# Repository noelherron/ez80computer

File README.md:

# eZ80Computer

This is a single board computer based on the Zilog eZ80 microcontroller.

The eZ80 was chosen because it is an interesting microcontroller with a deep history.

It's CPU is based on the Z80, which was very popular in the 1980s, and is still manufactured today.

The eZ80 is distinct from many other microcontrollers because it has an exposed address and data bus.

Most microcontrollers have built in memory and omit these pins.

This means we can design our own memory scheme, and learn about things like bus mastering.

Like a traditional microcontroller, it still has many built in periferals, which keeps things small and simple.

This is a learning project for me to better understand electronics, PCB design, and computer system design.

I have already spent many hours in KiCad and had a batch of prototypes made.

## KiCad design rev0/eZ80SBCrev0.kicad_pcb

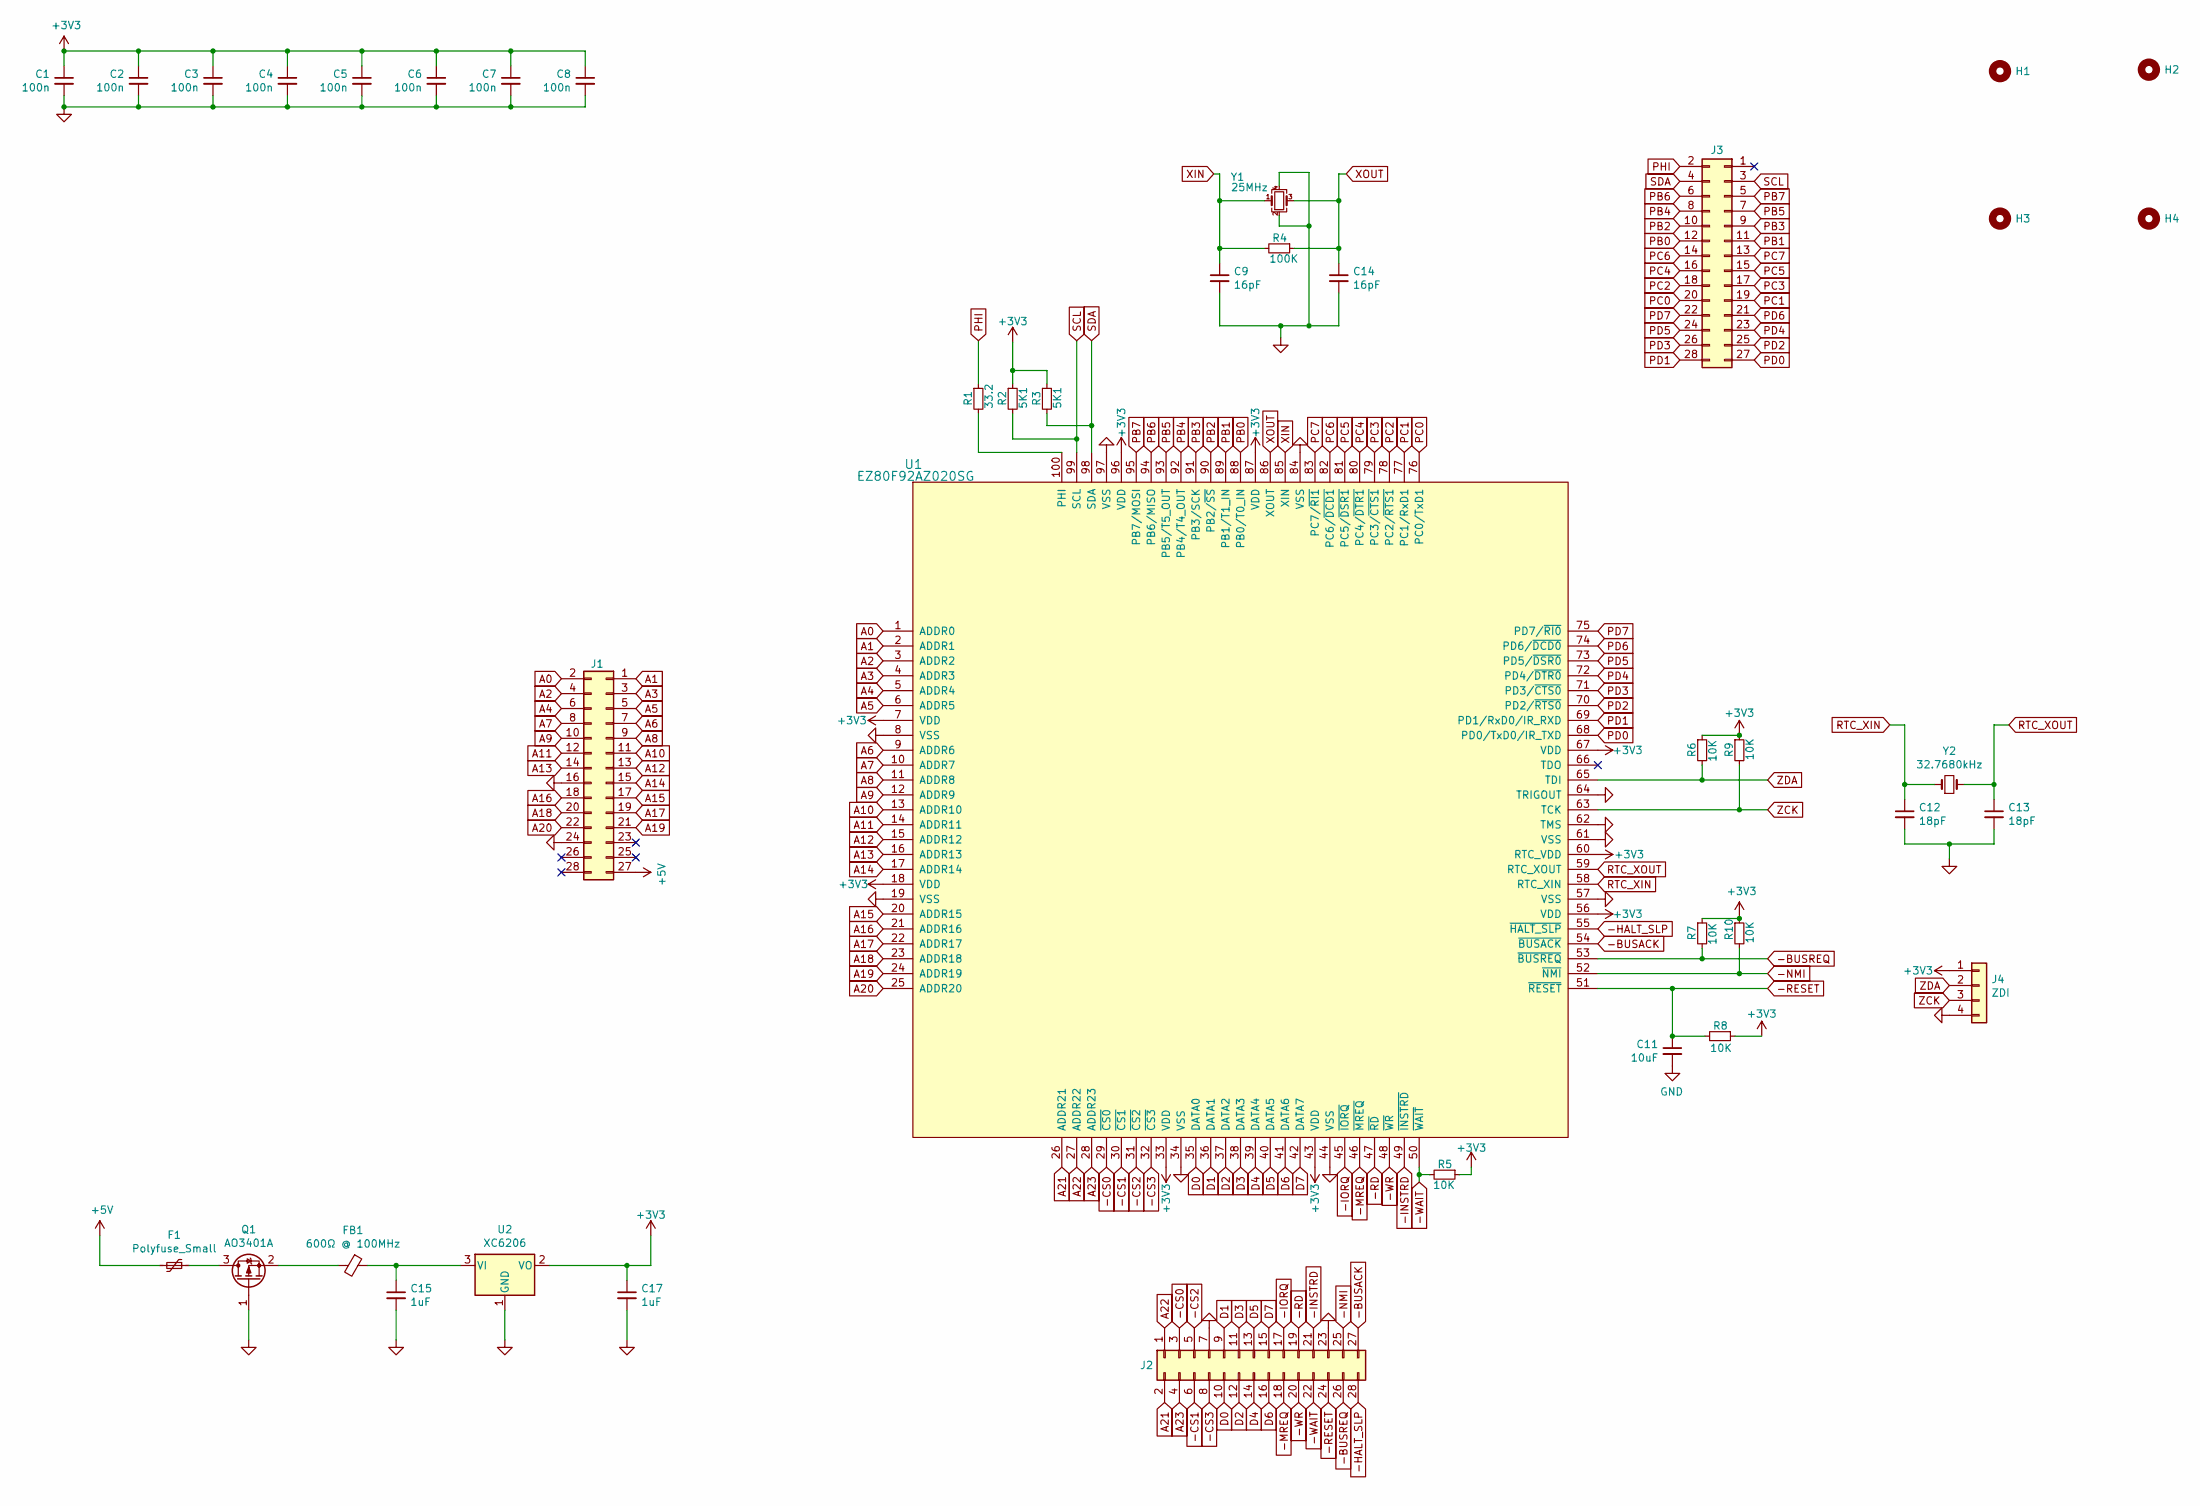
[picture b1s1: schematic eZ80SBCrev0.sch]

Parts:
C1, C2, C3, C4, C5, C6, C7, C8: 100n; C_0402_1005Metric; MFR. PART# CL05B104KO5NNNC; LCSC C1525
C9, C14: 16pF; C_0805_2012Metric; LCSC C1794
C11: 10uF; C_0402_1005Metric; MFR. PART# CL05A106MQ5NUNC; LCSC C15525
C12, C13: 18pF; C_0402_1005Metric; LCSC C1549
C15, C17: 1uF; C_0805_2012Metric; LCSC C28323
F1: Polyfuse_Small; Fuse_0805_2012Metric
FB1: 600Ω @ 100MHz; L_0805_2012Metric; LCSC C1017
H1, H2, H3, H4: MountingHole; MountingHole_2.1mm
J1, J2, J3: Conn_02x14_Top_Bottom; PinSocket_2x14_P2.54mm_Vertical
J4: ZDI; PinHeader_1x04_P2.54mm_Vertical
Q1: AO3401A; SOT-23; LCSC C15127
R1: 33.2; R_0402_1005Metric; MFR. PART# 0402WGF5101TCE; LCSC C25905
R2, R3: 5K1; R_0402_1005Metric; MFR. PART# 0402WGF5101TCE; LCSC C25905
R4: 100K; R_0805_2012Metric; LCSC C17407
R5, R6, R7, R8, R9, R10: 10K; R_0402_1005Metric; MFR. PART# 0402WGF1002TCE; LCSC C25744
U1: EZ80F92AZ020SG; LQFP-100_14x14mm_P0.5mm
U2: XC6206; SOT-23; LCSC C5446
Y1: 25MHz; SMD-5032-4P; LCSC C9006
Y2: 32.7680kHz; Crystal_SMD_3215-2Pin_3.2x1.5mm; LCSC C32346

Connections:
+3V3: C1.1, C2.1, C3.1, C4.1, C5.1, C6.1, C7.1, C8.1, C17.1, J4.1, R2.1, R3.1, R5.1, R6.1, R7.1, R8.1, R9.1, R10.1, U1.7 (VDD), U1.18 (VDD), U1.33 (VDD), U1.43 (VDD), U1.56 (VDD), U1.60 (RTC_VDD), U1.67 (VDD), U1.87 (VDD), U1.96 (VDD), U2.2 (VO)
+5V: F1.2, J1.27
-BUSACK: J2.27, U1.54 (~BUSACK)
-BUSREQ: J2.26, R7.2, U1.53 (~BUSREQ)
-CS0: J2.3, U1.29 (~CS0)
-CS1: J2.6, U1.30 (~CS1)
-CS2: J2.5, U1.31 (~CS2)
-CS3: J2.8, U1.32 (~CS3)
-HALT_SLP: J2.28, U1.55 (~HALT_SLP)
-INSTRD: J2.21, U1.49 (~INSTRD)
-IORQ: J2.17, U1.45 (~IORQ)
-MREQ: J2.18, U1.46 (~MREQ)
-NMI: J2.25, R10.2, U1.52 (~NMI)
-RD: J2.19, U1.47 (~RD)
-RESET: C11.1, J2.24, R8.2, U1.51 (~RESET)
-WAIT: J2.22, R5.2, U1.50 (~WAIT)
-WR: J2.20, U1.48 (~WR)
A0: J1.2, U1.1 (ADDR0)
A1: J1.1, U1.2 (ADDR1)
A2: J1.4, U1.3 (ADDR2)
A3: J1.3, U1.4 (ADDR3)
A4: J1.6, U1.5 (ADDR4)
A5: J1.5, U1.6 (ADDR5)
A6: J1.7, U1.9 (ADDR6)
A7: J1.8, U1.10 (ADDR7)
A8: J1.9, U1.11 (ADDR8)
A9: J1.10, U1.12 (ADDR9)
A10: J1.11, U1.13 (ADDR10)
A11: J1.12, U1.14 (ADDR11)
A12: J1.13, U1.15 (ADDR12)
A13: J1.14, U1.16 (ADDR13)
A14: J1.15, U1.17 (ADDR14)
A15: J1.17, U1.20 (ADDR15)
A16: J1.18, U1.21 (ADDR16)
A17: J1.19, U1.22 (ADDR17)
A18: J1.20, U1.23 (ADDR18)
A19: J1.21, U1.24 (ADDR19)
A20: J1.22, U1.25 (ADDR20)
A21: J2.2, U1.26 (ADDR21)
A22: J2.1, U1.27 (ADDR22)
A23: J2.4, U1.28 (ADDR23)
D0: J2.10, U1.35 (DATA0)
D1: J2.9, U1.36 (DATA1)
D2: J2.12, U1.37 (DATA2)
D3: J2.11, U1.38 (DATA3)
D4: J2.14, U1.39 (DATA4)
D5: J2.13, U1.40 (DATA5)
D6: J2.16, U1.41 (DATA6)
D7: J2.15, U1.42 (DATA7)
GND: C1.2, C2.2, C3.2, C4.2, C5.2, C6.2, C7.2, C8.2, C9.2, C11.2, C12.2, C13.2, C14.2, C15.2, C17.2, J1.16, J1.24, J2.7, J2.23, J4.4, Q1.1 (G), U1.8 (VSS), U1.19 (VSS), U1.34 (VSS), U1.44 (VSS), U1.57 (VSS), U1.61 (VSS), U1.62 (TMS), U1.64 (TRIGOUT), U1.84 (VSS), U1.97 (VSS), U2.1 (GND), Y1.2, Y1.4
unnamed: C15.1, FB1.1, U2.3 (VI)
unnamed: F1.1, Q1.3 (D)
unnamed: FB1.2, Q1.2 (S)
unnamed: R1.2, U1.100 (PHI)
PB0: J3.12, U1.88 (PB0/T0_IN)
PB1: J3.11, U1.89 (PB1/T1_IN)
PB2: J3.10, U1.90 (PB2/~SS)
PB3: J3.9, U1.91 (PB3/SCK)
PB4: J3.8, U1.92 (PB4/T4_OUT)
PB5: J3.7, U1.93 (PB5/T5_OUT)
PB6: J3.6, U1.94 (PB6/MISO)
PB7: J3.5, U1.95 (PB7/MOSI)
PC0: J3.20, U1.76 (PC0/TxD1)
PC1: J3.19, U1.77 (PC1/RxD1)
PC2: J3.18, U1.78 (PC2/~RTS1)
PC3: J3.17, U1.79 (PC3/~CTS1)
PC4: J3.16, U1.80 (PC4/~DTR1)
PC5: J3.15, U1.81 (PC5/~DSR1)
PC6: J3.14, U1.82 (PC6/~DCD1)
PC7: J3.13, U1.83 (PC7/~RI1)
PD0: J3.27, U1.68 (PD0/TxD0/IR_TXD)
PD1: J3.28, U1.69 (PD1/RxD0/IR_RXD)
PD2: J3.25, U1.70 (PD2/~RTS0)
PD3: J3.26, U1.71 (PD3/~CTS0)
PD4: J3.23, U1.72 (PD4/~DTR0)
PD5: J3.24, U1.73 (PD5/~DSR0)
PD6: J3.21, U1.74 (PD6/~DCD0)
PD7: J3.22, U1.75 (PD7/~RI0)
PHI: J3.2, R1.1
RTC_XIN: C12.1, U1.58 (RTC_XIN), Y2.1
RTC_XOUT: C13.1, U1.59 (RTC_XOUT), Y2.2
SCL: J3.3, R2.2, U1.99 (SCL)
SDA: J3.4, R3.2, U1.98 (SDA)
XIN: C9.1, R4.2, U1.85 (XIN), Y1.1
XOUT: C14.1, R4.1, U1.86 (XOUT), Y1.3
ZCK: J4.3, R9.2, U1.63 (TCK)
ZDA: J4.2, R6.2, U1.65 (TDI)

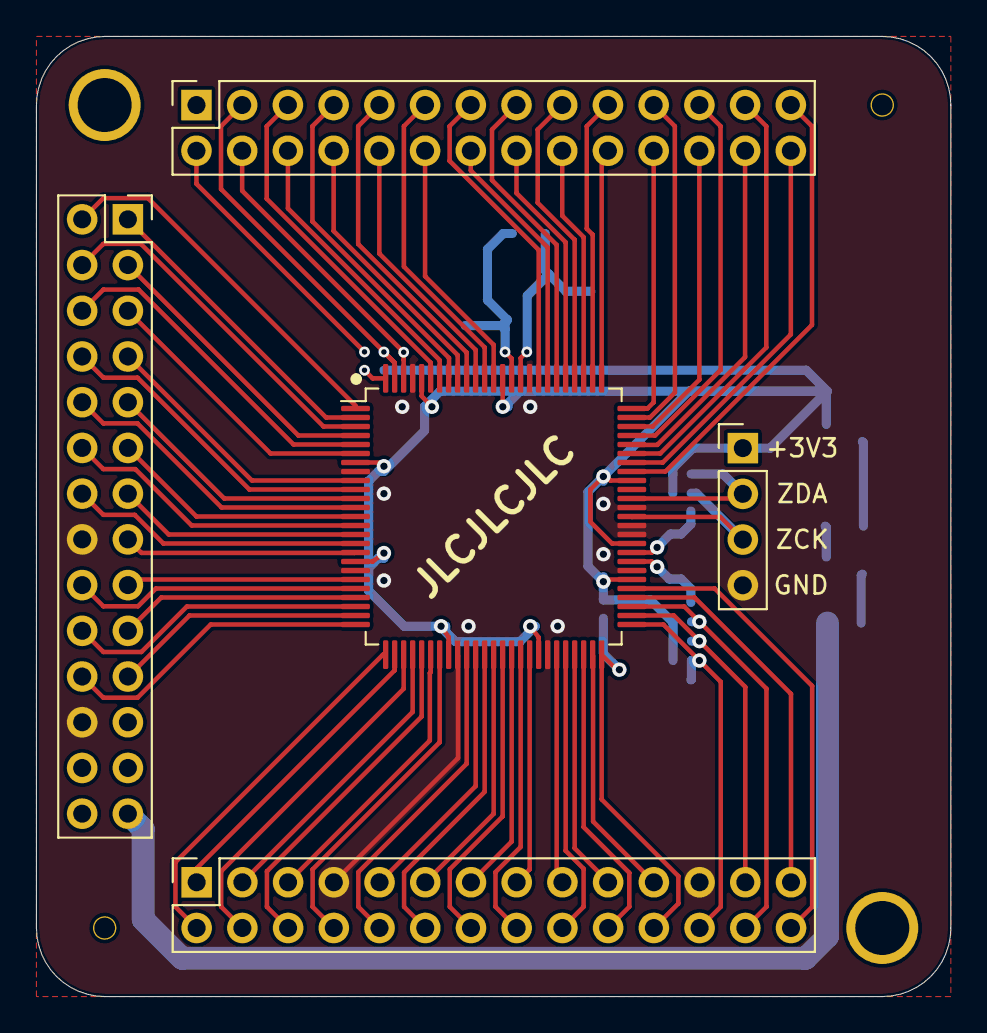
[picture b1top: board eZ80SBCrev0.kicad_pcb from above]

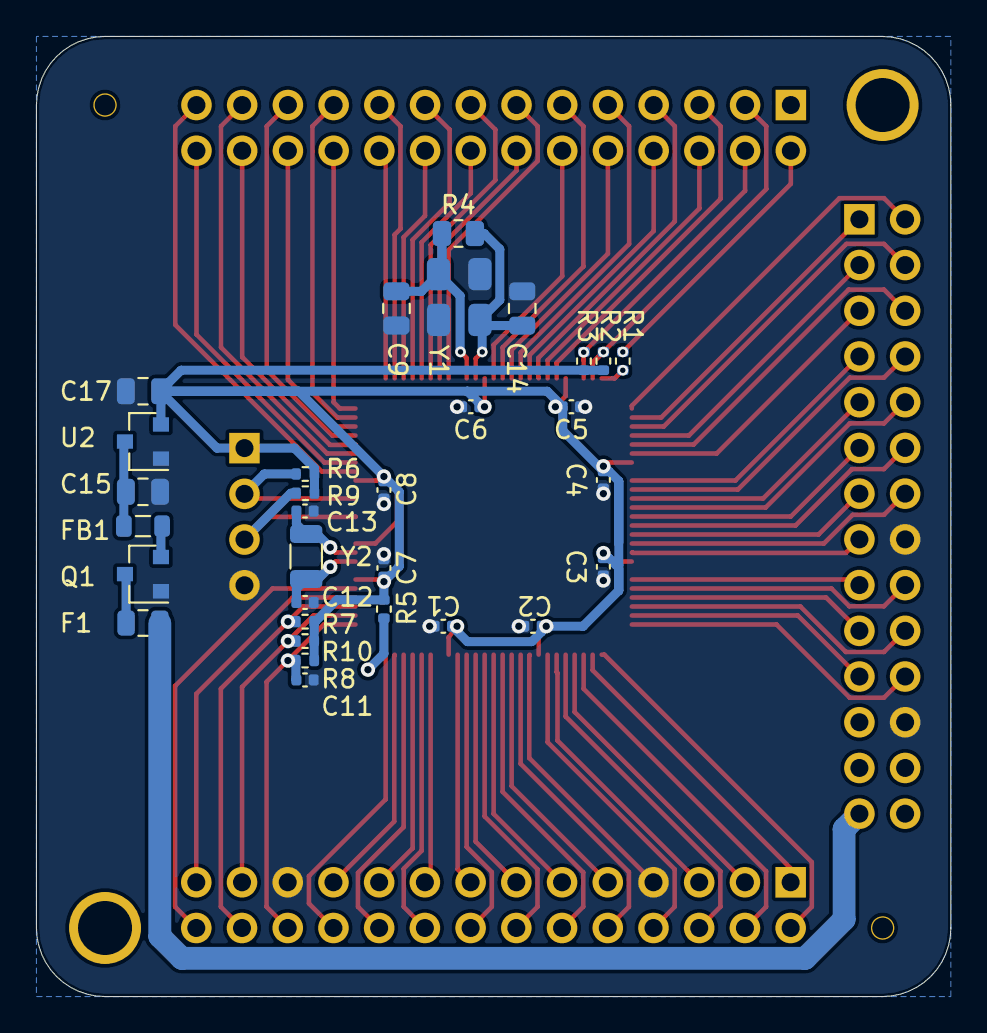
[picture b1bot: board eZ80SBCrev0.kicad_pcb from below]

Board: 2 copper layers, 50.8 x 53.3 mm, 40 parts (31 on the bottom side), 87 nets.

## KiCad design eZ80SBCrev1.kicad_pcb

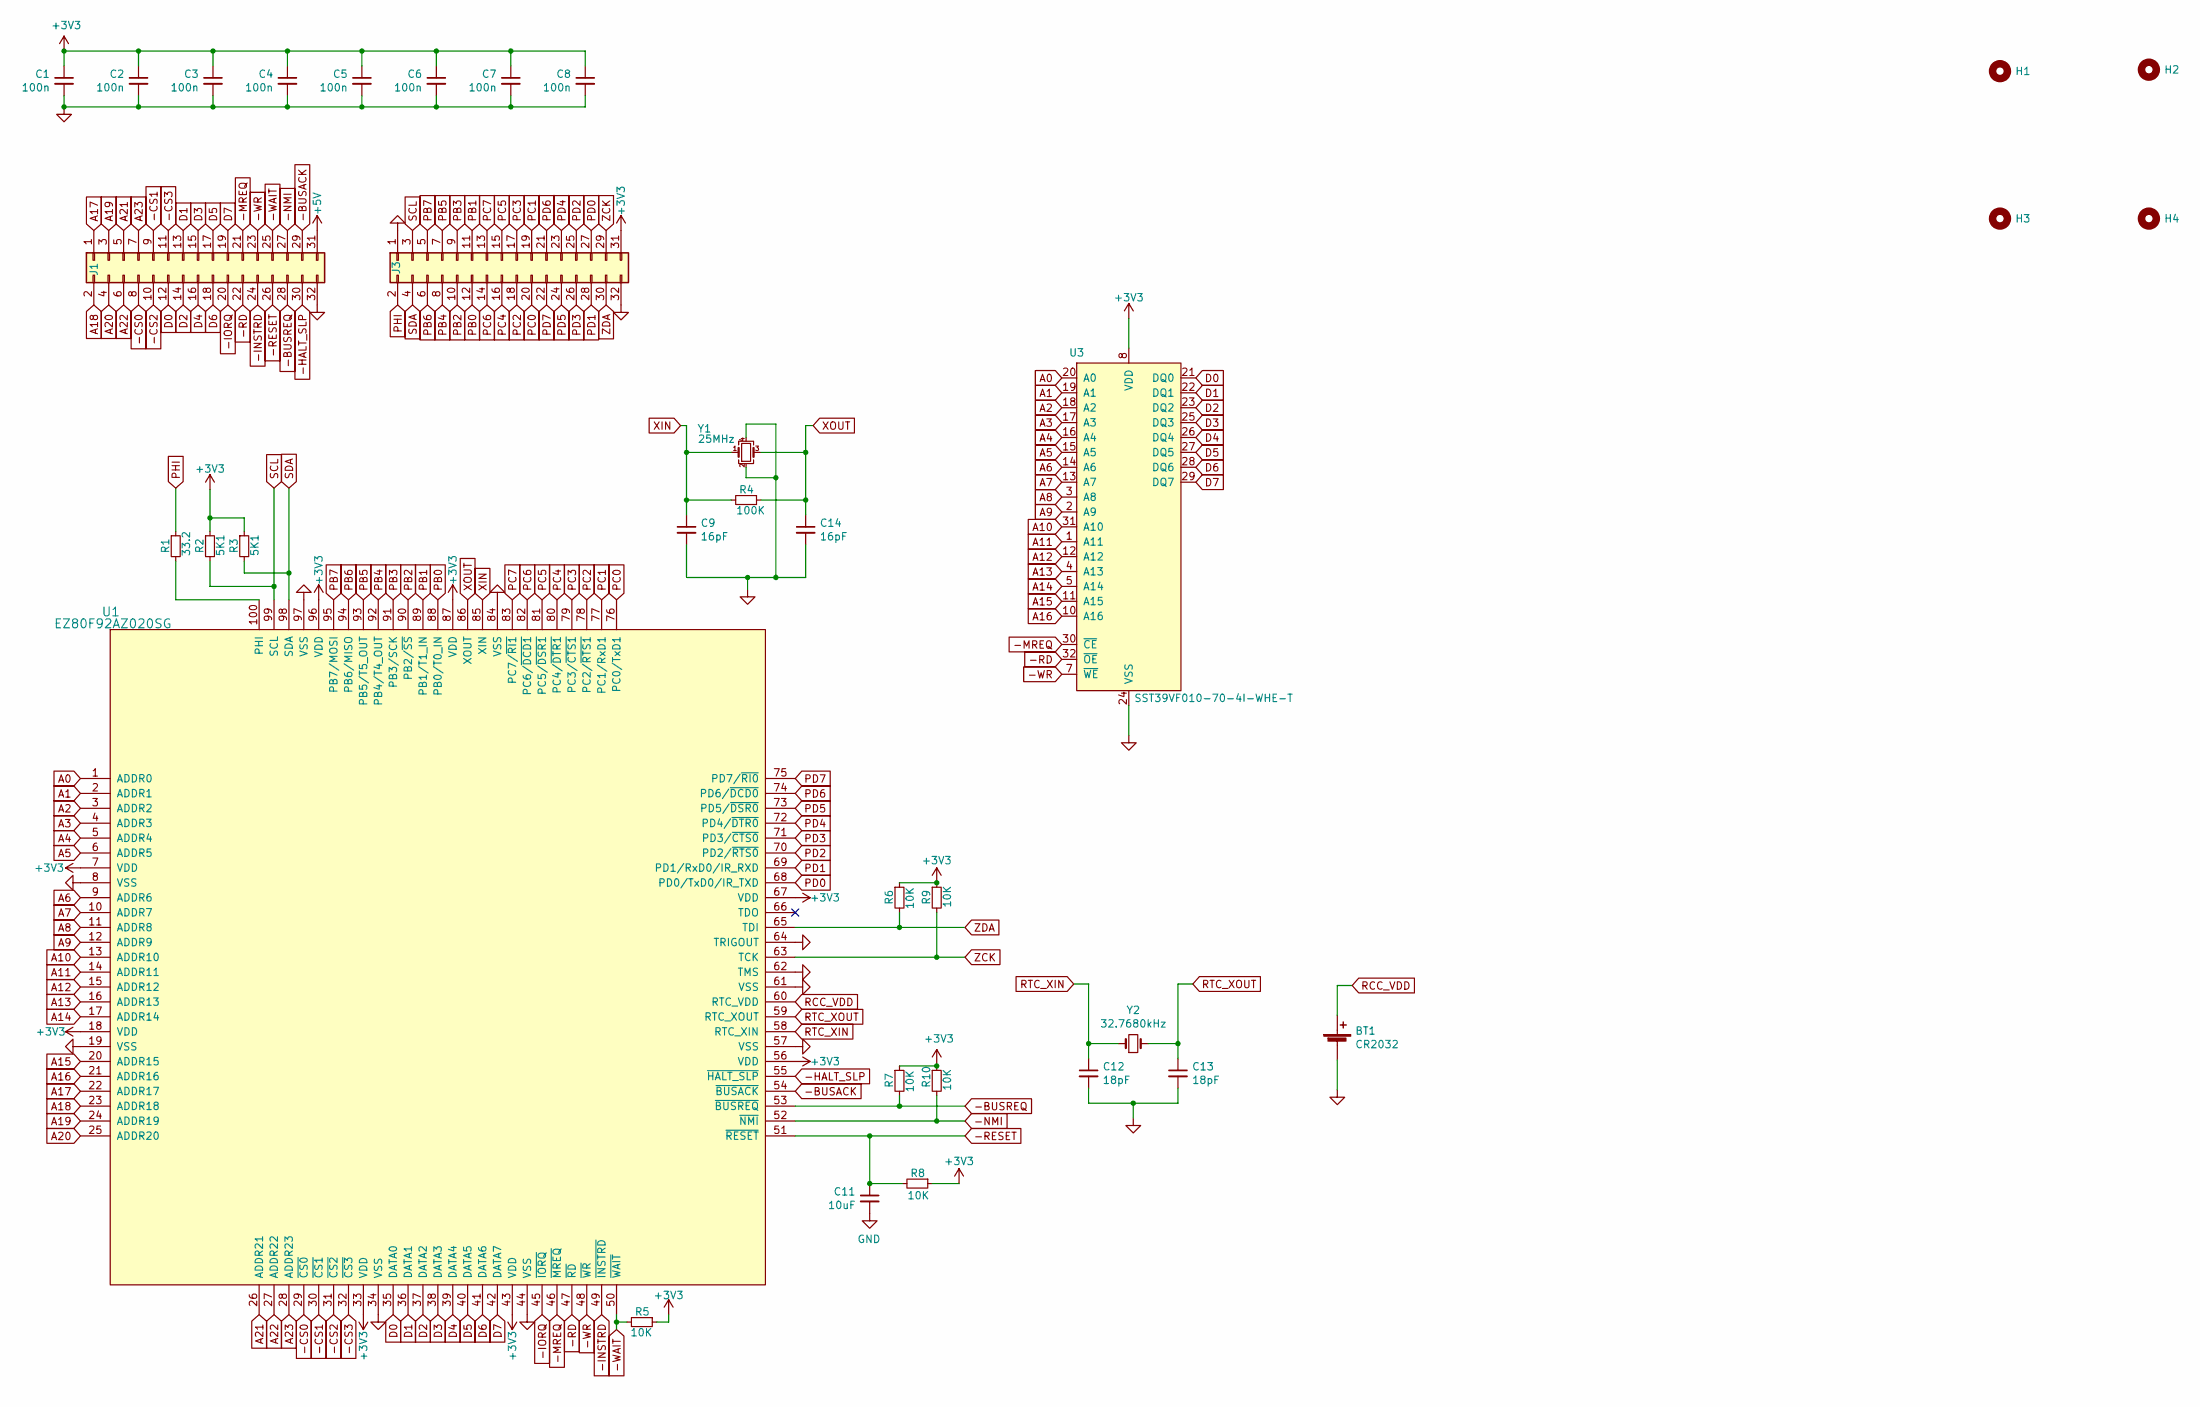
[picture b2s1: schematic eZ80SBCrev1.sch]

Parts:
BT1: CR2032; BatteryHolder_Keystone_3034_1x20mm
C1, C2, C3, C4, C5, C6, C7, C8: 100n; C_0402_1005Metric; MFR. PART# CL05B104KO5NNNC; LCSC C1525
C9, C14: 16pF; C_0805_2012Metric; LCSC C1794
C11: 10uF; C_0402_1005Metric; MFR. PART# CL05A106MQ5NUNC; LCSC C15525
C12, C13: 18pF; C_0402_1005Metric; LCSC C1549
H1, H2, H3, H4: MountingHole; MountingHole_2.1mm
J1, J3: Conn_02x16_Top_Bottom; PinSocket_2x16_P2.54mm_Vertical
R1: 33.2; R_0402_1005Metric; MFR. PART# 0402WGF5101TCE; LCSC C25905
R2, R3: 5K1; R_0402_1005Metric; MFR. PART# 0402WGF5101TCE; LCSC C25905
R4: 100K; R_0805_2012Metric; LCSC C17407
R5, R6, R7, R8, R9, R10: 10K; R_0402_1005Metric; MFR. PART# 0402WGF1002TCE; LCSC C25744
U1: EZ80F92AZ020SG; LQFP-100_14x14mm_P0.5mm
U3: SST39VF010-70-4I-WHE-T; TSOP-I-32_11.8x8mm_P0.5mm
Y1: 25MHz; SMD-5032-4P; LCSC C9006
Y2: 32.7680kHz; Crystal_SMD_3215-2Pin_3.2x1.5mm; LCSC C32346

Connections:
+3V3: C1.1, C2.1, C3.1, C4.1, C5.1, C6.1, C7.1, C8.1, J3.31, R2.1, R3.1, R5.1, R6.1, R7.1, R8.1, R9.1, R10.1, U1.7 (VDD), U1.18 (VDD), U1.33 (VDD), U1.43 (VDD), U1.56 (VDD), U1.67 (VDD), U1.87 (VDD), U1.96 (VDD), U3.8 (VDD)
-BUSACK: J1.29, U1.54 (~BUSACK)
-BUSREQ: J1.28, R7.2, U1.53 (~BUSREQ)
-CS0: J1.8, U1.29 (~CS0)
-CS1: J1.9, U1.30 (~CS1)
-CS2: J1.10, U1.31 (~CS2)
-CS3: J1.11, U1.32 (~CS3)
-HALT_SLP: J1.30, U1.55 (~HALT_SLP)
-INSTRD: J1.24, U1.49 (~INSTRD)
-IORQ: J1.20, U1.45 (~IORQ)
-MREQ: J1.21, U1.46 (~MREQ), U3.30 (~CE)
-NMI: J1.27, R10.2, U1.52 (~NMI)
-RD: J1.22, U1.47 (~RD), U3.32 (~OE)
-RESET: C11.1, J1.26, R8.2, U1.51 (~RESET)
-WAIT: J1.25, R5.2, U1.50 (~WAIT)
-WR: J1.23, U1.48 (~WR), U3.7 (~WE)
A0: U1.1 (ADDR0), U3.20 (A0)
A1: U1.2 (ADDR1), U3.19 (A1)
A2: U1.3 (ADDR2), U3.18 (A2)
A3: U1.4 (ADDR3), U3.17 (A3)
A4: U1.5 (ADDR4), U3.16 (A4)
A5: U1.6 (ADDR5), U3.15 (A5)
A6: U1.9 (ADDR6), U3.14 (A6)
A7: U1.10 (ADDR7), U3.13 (A7)
A8: U1.11 (ADDR8), U3.3 (A8)
A9: U1.12 (ADDR9), U3.2 (A9)
A10: U1.13 (ADDR10), U3.31 (A10)
A11: U1.14 (ADDR11), U3.1 (A11)
A12: U1.15 (ADDR12), U3.12 (A12)
A13: U1.16 (ADDR13), U3.4 (A13)
A14: U1.17 (ADDR14), U3.5 (A14)
A15: U1.20 (ADDR15), U3.11 (A15)
A16: U1.21 (ADDR16), U3.10 (A16)
A17: J1.1, U1.22 (ADDR17)
A18: J1.2, U1.23 (ADDR18)
A19: J1.3, U1.24 (ADDR19)
A20: J1.4, U1.25 (ADDR20)
A21: J1.5, U1.26 (ADDR21)
A22: J1.6, U1.27 (ADDR22)
A23: J1.7, U1.28 (ADDR23)
D0: J1.12, U1.35 (DATA0), U3.21 (DQ0)
D1: J1.13, U1.36 (DATA1), U3.22 (DQ1)
D2: J1.14, U1.37 (DATA2), U3.23 (DQ2)
D3: J1.15, U1.38 (DATA3), U3.25 (DQ3)
D4: J1.16, U1.39 (DATA4), U3.26 (DQ4)
D5: J1.17, U1.40 (DATA5), U3.27 (DQ5)
D6: J1.18, U1.41 (DATA6), U3.28 (DQ6)
D7: J1.19, U1.42 (DATA7), U3.29 (DQ7)
GND: BT1.2 (-), C1.2, C2.2, C3.2, C4.2, C5.2, C6.2, C7.2, C8.2, C9.2, C11.2, C12.2, C13.2, C14.2, J1.32, J3.1, J3.32, U1.8 (VSS), U1.19 (VSS), U1.34 (VSS), U1.44 (VSS), U1.57 (VSS), U1.61 (VSS), U1.62 (TMS), U1.64 (TRIGOUT), U1.84 (VSS), U1.97 (VSS), U3.24 (VSS), Y1.2, Y1.4
unnamed: R1.2, U1.100 (PHI)
PB0: J3.12, U1.88 (PB0/T0_IN)
PB1: J3.11, U1.89 (PB1/T1_IN)
PB2: J3.10, U1.90 (PB2/~SS)
PB3: J3.9, U1.91 (PB3/SCK)
PB4: J3.8, U1.92 (PB4/T4_OUT)
PB5: J3.7, U1.93 (PB5/T5_OUT)
PB6: J3.6, U1.94 (PB6/MISO)
PB7: J3.5, U1.95 (PB7/MOSI)
PC0: J3.20, U1.76 (PC0/TxD1)
PC1: J3.19, U1.77 (PC1/RxD1)
PC2: J3.18, U1.78 (PC2/~RTS1)
PC3: J3.17, U1.79 (PC3/~CTS1)
PC4: J3.16, U1.80 (PC4/~DTR1)
PC5: J3.15, U1.81 (PC5/~DSR1)
PC6: J3.14, U1.82 (PC6/~DCD1)
PC7: J3.13, U1.83 (PC7/~RI1)
PD0: J3.27, U1.68 (PD0/TxD0/IR_TXD)
PD1: J3.28, U1.69 (PD1/RxD0/IR_RXD)
PD2: J3.25, U1.70 (PD2/~RTS0)
PD3: J3.26, U1.71 (PD3/~CTS0)
PD4: J3.23, U1.72 (PD4/~DTR0)
PD5: J3.24, U1.73 (PD5/~DSR0)
PD6: J3.21, U1.74 (PD6/~DCD0)
PD7: J3.22, U1.75 (PD7/~RI0)
PHI: J3.2, R1.1
RCC_VDD: BT1.1 (+), U1.60 (RTC_VDD)
RTC_XIN: C12.1, U1.58 (RTC_XIN), Y2.1
RTC_XOUT: C13.1, U1.59 (RTC_XOUT), Y2.2
SCL: J3.3, R2.2, U1.99 (SCL)
SDA: J3.4, R3.2, U1.98 (SDA)
XIN: C9.1, R4.2, U1.85 (XIN), Y1.1
XOUT: C14.1, R4.1, U1.86 (XOUT), Y1.3
ZCK: J3.29, R9.2, U1.63 (TCK)
ZDA: J3.30, R6.2, U1.65 (TDI)

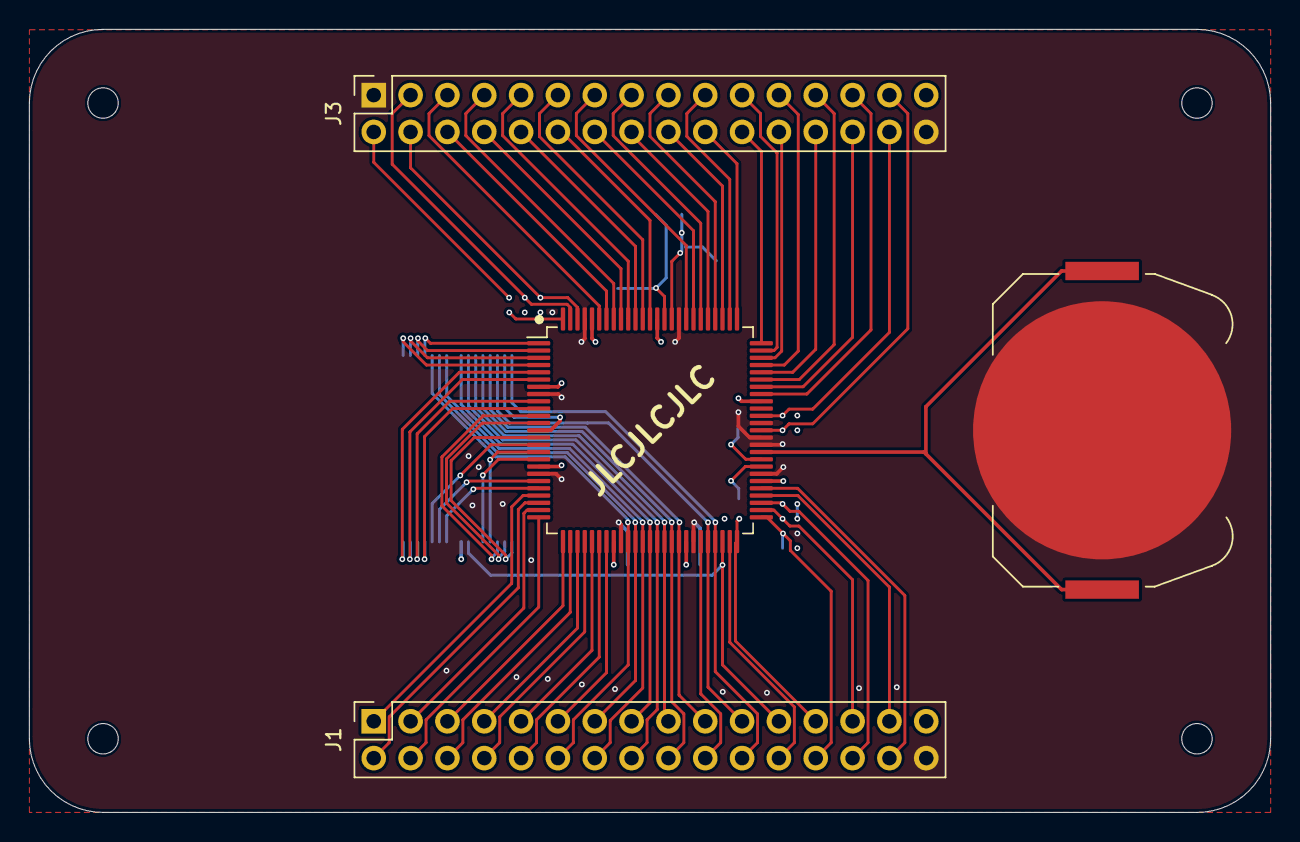
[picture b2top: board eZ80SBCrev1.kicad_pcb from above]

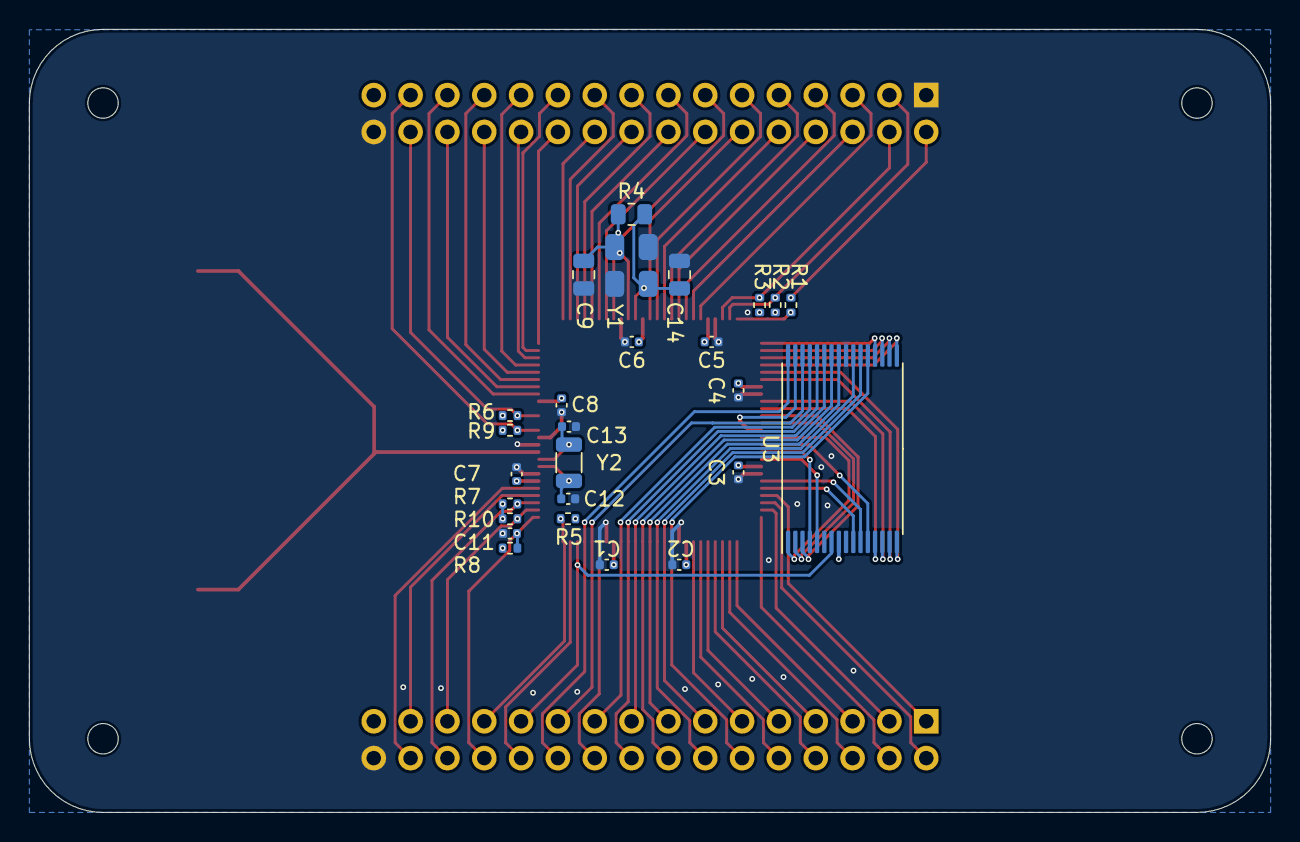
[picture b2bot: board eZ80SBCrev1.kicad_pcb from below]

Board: 4 copper layers, 85.6 x 54.0 mm, 34 parts (26 on the bottom side), 84 nets.

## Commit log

2021-07-15 Create ez80SBCrev0
